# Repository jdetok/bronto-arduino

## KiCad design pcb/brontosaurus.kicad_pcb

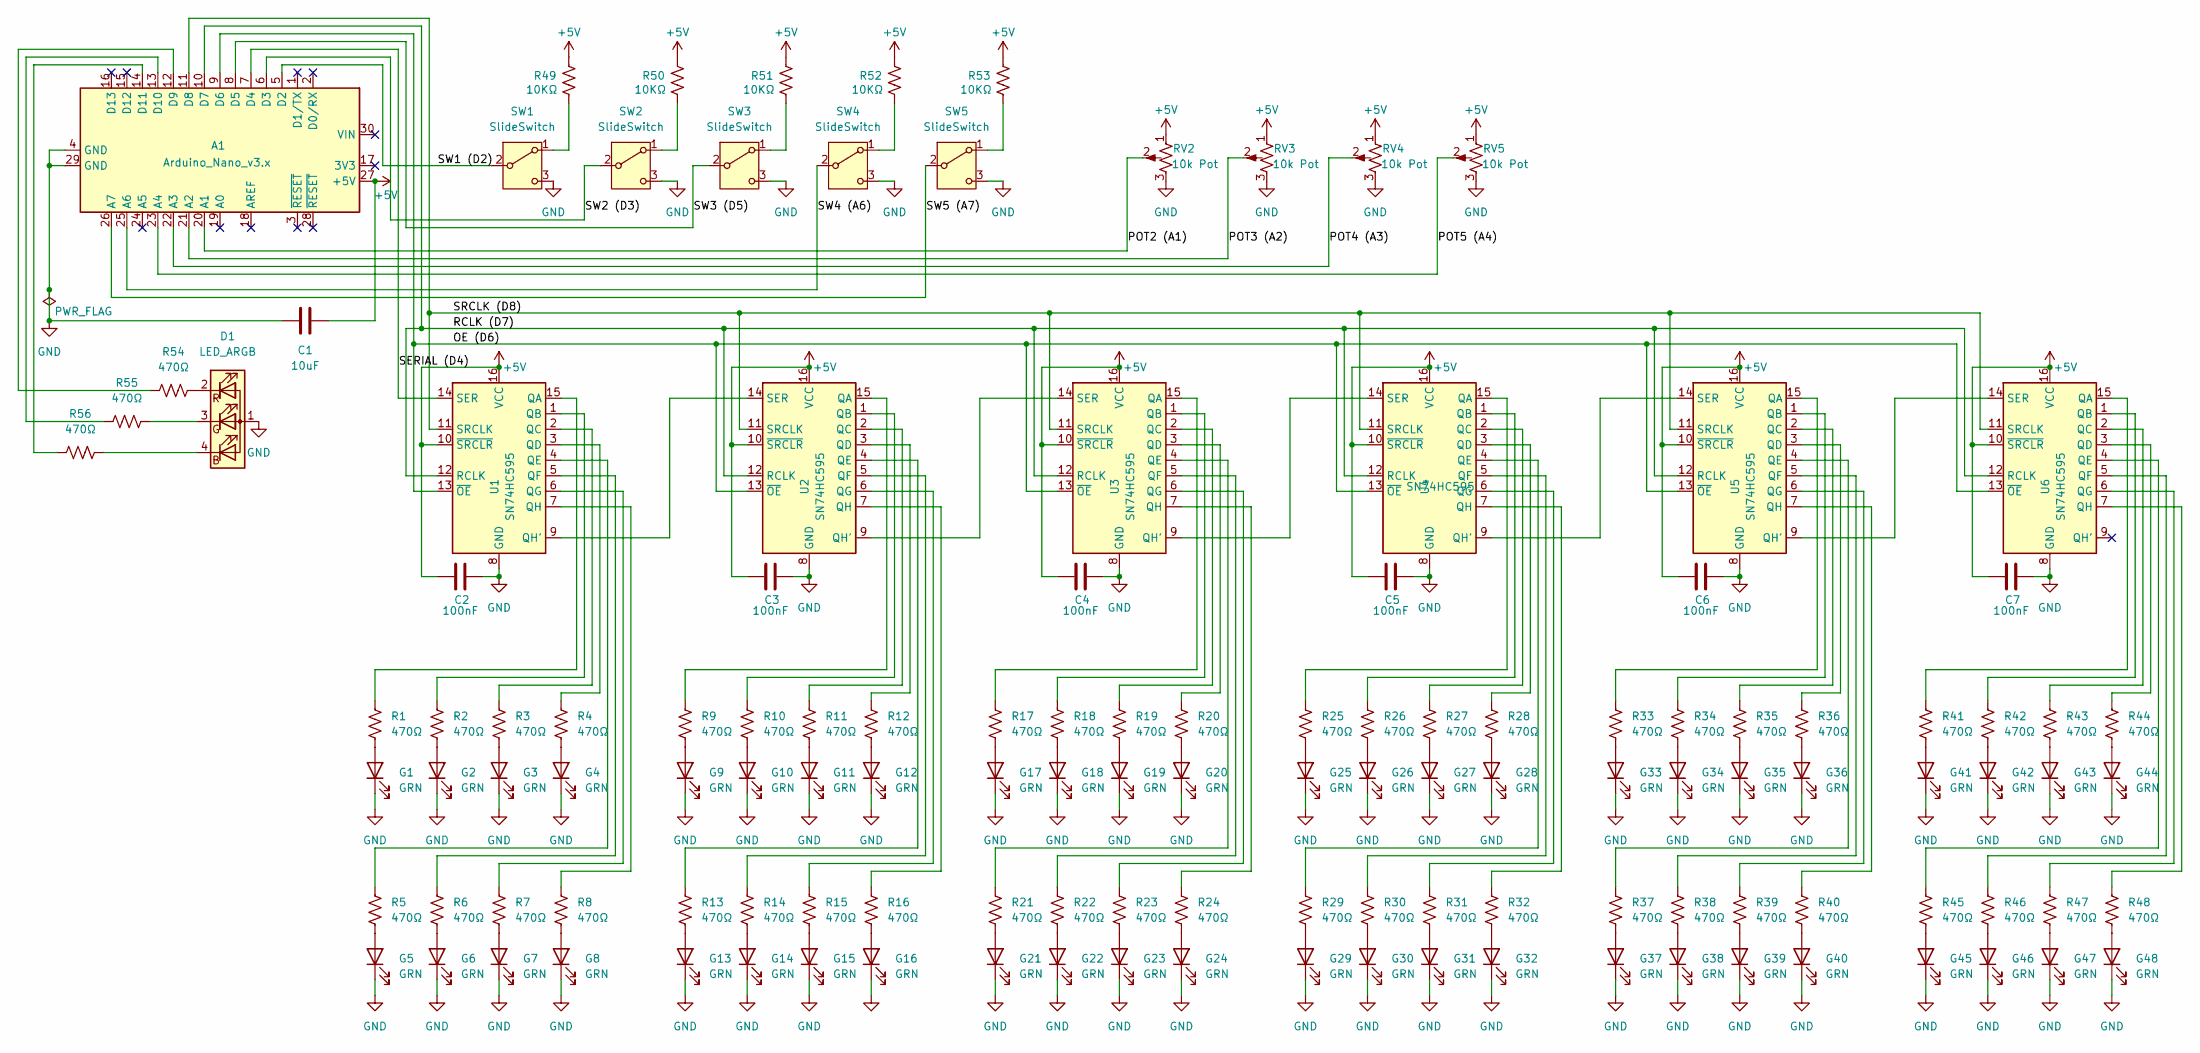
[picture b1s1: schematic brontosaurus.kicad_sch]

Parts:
A1: Arduino_Nano_v3.x; Arduino_Nano
C1: 10uF; C_Radial_D4.0mm_H5.0mm_P1.50mm
C2, C3, C4, C5, C6, C7: 100nF; C_Disc_D5.0mm_W2.5mm_P5.00mm
D1: LED_ARGB; LED_D5.0mm-4_RGB_Wide_Pins
G1, G2, G3, G4, G5, G6, G7, G8, G9, G10, G11, G12, G13, G14, G15, G16, G17, G18, G19, G20, G21, G22, G23, G24, G25, G26, G27, G28, G29, G30, G31, G32, G33, G34, G35, G36, G37, G38, G39, G40, G41, G42, G43, G44, G45, G46, G47, G48: GRN; LED_D5.0mm_Clear
R1, R2, R3, R4, R5, R6, R7, R8, R9, R10, R11, R12, R13, R14, R15, R16, R17, R18, R19, R20, R21, R22, R23, R24, R25, R26, R27, R28, R29, R30, R31, R32, R33, R34, R35, R36, R37, R38, R39, R40, R41, R42, R43, R44, R45, R46, R47, R48, R54, R55, R56: 470Ω; R_Axial_DIN0204_L3.6mm_D1.6mm_P7.62mm_Horizontal
R49, R50, R51, R52, R53: 10KΩ; R_Axial_DIN0204_L3.6mm_D1.6mm_P7.62mm_Horizontal
RV2, RV3, RV4, RV5: 10k Pot; pot_left
SW1, SW2, SW3, SW4, SW5: SlideSwitch; SlideSwitch3Pin
U1, U2, U3, U4, U5, U6: SN74HC595; 74HC595_7.62mm

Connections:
+5V: A1.27 (+5V), C1.2, C2.1, C3.1, C4.1, C5.1, C6.1, C7.1, R49.1, R50.1, R51.1, R52.1, R53.1, RV2.1, RV3.1, RV4.1, RV5.1, U1.10 (~SRCLR), U1.16 (VCC), U2.10 (~SRCLR), U2.16 (VCC), U3.10 (~SRCLR), U3.16 (VCC), U4.10 (~SRCLR), U4.16 (VCC), U5.10 (~SRCLR), U5.16 (VCC), U6.10 (~SRCLR), U6.16 (VCC)
/OE (D6): A1.9 (D6), U1.13 (~OE), U2.13 (~OE), U3.13 (~OE), U4.13 (~OE), U5.13 (~OE), U6.13 (~OE)
/POT2 (A1): A1.20 (A1), RV2.2
/POT3 (A2): A1.21 (A2), RV3.2
/POT4 (A3): A1.22 (A3), RV4.2
/POT5 (A4): A1.23 (A4), RV5.2
/RCLK (D7): A1.10 (D7), U1.12 (RCLK), U2.12 (RCLK), U3.12 (RCLK), U4.12 (RCLK), U5.12 (RCLK), U6.12 (RCLK)
/SERIAL (D4): A1.7 (D4), U1.14 (SER)
/SRCLK (D8): A1.11 (D8), U1.11 (SRCLK), U2.11 (SRCLK), U3.11 (SRCLK), U4.11 (SRCLK), U5.11 (SRCLK), U6.11 (SRCLK)
/SW1 (D2): A1.5 (D2), SW1.2 (B)
/SW2 (D3): A1.6 (D3), SW2.2 (B)
/SW3 (D5): A1.8 (D5), SW3.2 (B)
/SW4 (A6): A1.25 (A6), SW4.2 (B)
/SW5 (A7): A1.26 (A7), SW5.2 (B)
GND: A1.4 (GND), A1.29 (GND), C1.1, C2.2, C3.2, C4.2, C5.2, C6.2, C7.2, D1.1 (A), G1.1 (K), G2.1 (K), G3.1 (K), G4.1 (K), G5.1 (K), G6.1 (K), G7.1 (K), G8.1 (K), G9.1 (K), G10.1 (K), G11.1 (K), G12.1 (K), G13.1 (K), G14.1 (K), G15.1 (K), G16.1 (K), G17.1 (K), G18.1 (K), G19.1 (K), G20.1 (K), G21.1 (K), G22.1 (K), G23.1 (K), G24.1 (K), G25.1 (K), G26.1 (K), G27.1 (K), G28.1 (K), G29.1 (K), G30.1 (K), G31.1 (K), G32.1 (K), G33.1 (K), G34.1 (K), G35.1 (K), G36.1 (K), G37.1 (K), G38.1 (K), G39.1 (K), G40.1 (K), G41.1 (K), G42.1 (K), G43.1 (K), G44.1 (K), G45.1 (K), G46.1 (K), G47.1 (K), G48.1 (K), RV2.3, RV3.3, RV4.3, RV5.3, SW1.3 (C), SW2.3 (C), SW3.3 (C), SW4.3 (C), SW5.3 (C), U1.8 (GND), U2.8 (GND), U3.8 (GND), U4.8 (GND), U5.8 (GND), U6.8 (GND)
unnamed: A1.12 (D9), R54.1
unnamed: A1.13 (D10), R55.1
unnamed: A1.14 (D11), R56.1
unnamed: D1.4 (BK), R56.2
unnamed: D1.3 (GK), R55.2
unnamed: D1.2 (RK), R54.2
unnamed: G1.2 (A), R1.2
unnamed: G2.2 (A), R2.2
unnamed: G3.2 (A), R3.2
unnamed: G4.2 (A), R4.2
unnamed: G5.2 (A), R5.2
unnamed: G6.2 (A), R6.2
unnamed: G7.2 (A), R7.2
unnamed: G8.2 (A), R8.2
unnamed: G9.2 (A), R9.2
unnamed: G10.2 (A), R10.2
unnamed: G11.2 (A), R11.2
unnamed: G12.2 (A), R12.2
unnamed: G13.2 (A), R13.2
unnamed: G14.2 (A), R14.2
unnamed: G15.2 (A), R15.2
unnamed: G16.2 (A), R16.2
unnamed: G17.2 (A), R17.2
unnamed: G18.2 (A), R18.2
unnamed: G19.2 (A), R19.2
unnamed: G20.2 (A), R20.2
unnamed: G21.2 (A), R21.2
unnamed: G22.2 (A), R22.2
unnamed: G23.2 (A), R23.2
unnamed: G24.2 (A), R24.2
unnamed: G25.2 (A), R25.2
unnamed: G26.2 (A), R26.2
unnamed: G27.2 (A), R27.2
unnamed: G28.2 (A), R28.2
unnamed: G29.2 (A), R29.2
unnamed: G30.2 (A), R30.2
unnamed: G31.2 (A), R31.2
unnamed: G32.2 (A), R32.2
unnamed: G33.2 (A), R33.2
unnamed: G34.2 (A), R34.2
unnamed: G35.2 (A), R35.2
unnamed: G36.2 (A), R36.2
unnamed: G37.2 (A), R37.2
unnamed: G38.2 (A), R38.2
unnamed: G39.2 (A), R39.2
unnamed: G40.2 (A), R40.2
unnamed: G41.2 (A), R41.2
unnamed: G42.2 (A), R42.2
unnamed: G43.2 (A), R43.2
unnamed: G44.2 (A), R44.2
unnamed: G45.2 (A), R45.2
unnamed: G46.2 (A), R46.2
unnamed: G47.2 (A), R47.2
unnamed: G48.2 (A), R48.2
unnamed: R49.2, SW1.1 (A)
unnamed: R50.2, SW2.1 (A)
unnamed: R51.2, SW3.1 (A)
unnamed: R52.2, SW4.1 (A)
unnamed: R53.2, SW5.1 (A)
unnamed: R1.1, U1.15 (QA)
unnamed: R2.1, U1.1 (QB)
unnamed: R3.1, U1.2 (QC)
unnamed: R4.1, U1.3 (QD)
unnamed: R5.1, U1.4 (QE)
unnamed: R6.1, U1.5 (QF)
unnamed: R7.1, U1.6 (QG)
unnamed: U1.9 (QH'), U2.14 (SER)
unnamed: R8.1, U1.7 (QH)
unnamed: R9.1, U2.15 (QA)
unnamed: R10.1, U2.1 (QB)
unnamed: R11.1, U2.2 (QC)
unnamed: R12.1, U2.3 (QD)
unnamed: R13.1, U2.4 (QE)
unnamed: R14.1, U2.5 (QF)
unnamed: R15.1, U2.6 (QG)
unnamed: U2.9 (QH'), U3.14 (SER)
unnamed: R16.1, U2.7 (QH)
unnamed: R17.1, U3.15 (QA)
unnamed: R18.1, U3.1 (QB)
unnamed: R19.1, U3.2 (QC)
unnamed: R20.1, U3.3 (QD)
unnamed: R21.1, U3.4 (QE)
unnamed: R22.1, U3.5 (QF)
unnamed: R23.1, U3.6 (QG)
unnamed: U3.9 (QH'), U4.14 (SER)
unnamed: R24.1, U3.7 (QH)
unnamed: R25.1, U4.15 (QA)
unnamed: R26.1, U4.1 (QB)
unnamed: R27.1, U4.2 (QC)
unnamed: R28.1, U4.3 (QD)
unnamed: R29.1, U4.4 (QE)
unnamed: R30.1, U4.5 (QF)
unnamed: R31.1, U4.6 (QG)
unnamed: U4.9 (QH'), U5.14 (SER)
unnamed: R32.1, U4.7 (QH)
unnamed: R33.1, U5.15 (QA)
unnamed: R34.1, U5.1 (QB)
unnamed: R35.1, U5.2 (QC)
unnamed: R36.1, U5.3 (QD)
unnamed: R37.1, U5.4 (QE)
unnamed: R38.1, U5.5 (QF)
unnamed: R39.1, U5.6 (QG)
unnamed: U5.9 (QH'), U6.14 (SER)
unnamed: R40.1, U5.7 (QH)
unnamed: R41.1, U6.15 (QA)
unnamed: R42.1, U6.1 (QB)
unnamed: R43.1, U6.2 (QC)
unnamed: R44.1, U6.3 (QD)
unnamed: R45.1, U6.4 (QE)
unnamed: R46.1, U6.5 (QF)
unnamed: R47.1, U6.6 (QG)
unnamed: R48.1, U6.7 (QH)

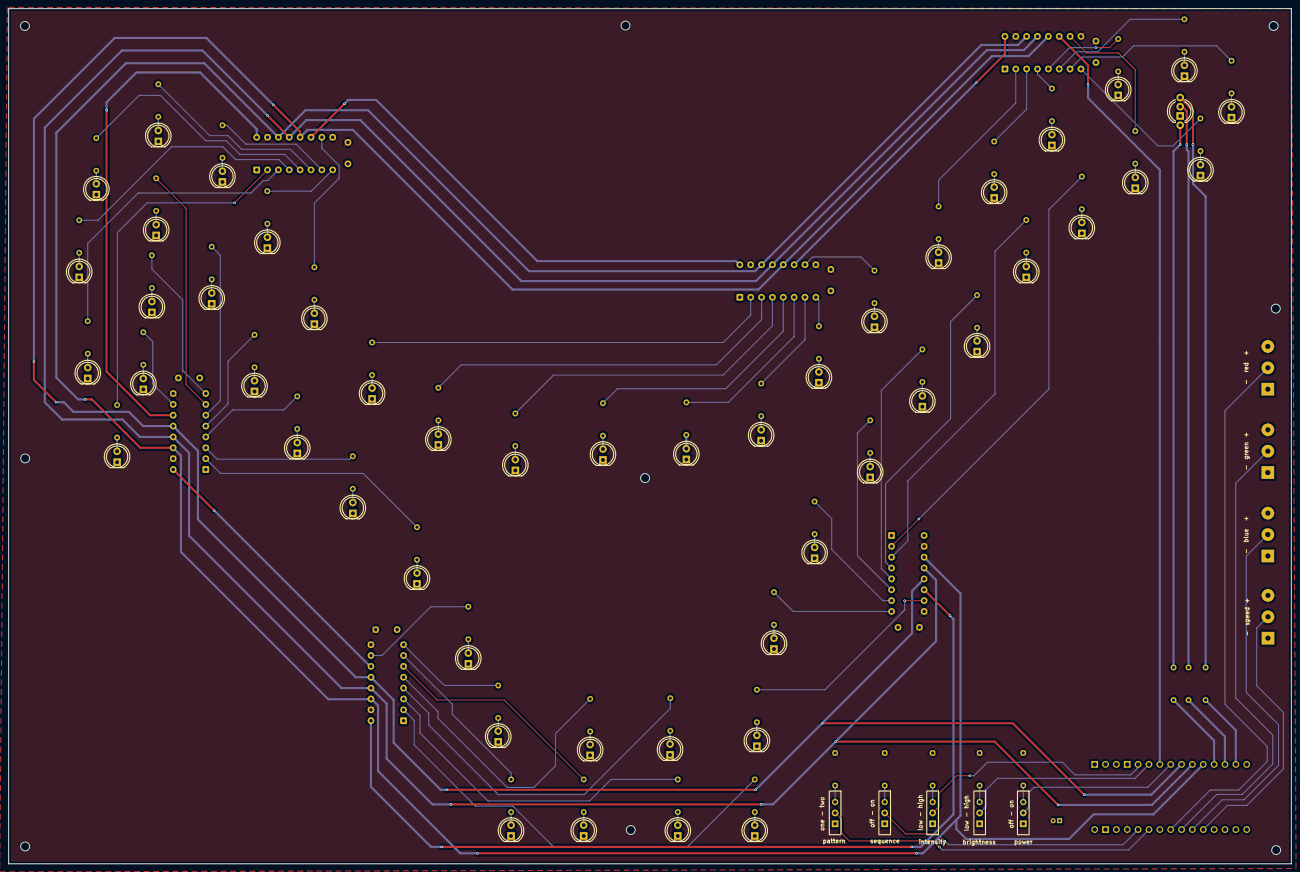
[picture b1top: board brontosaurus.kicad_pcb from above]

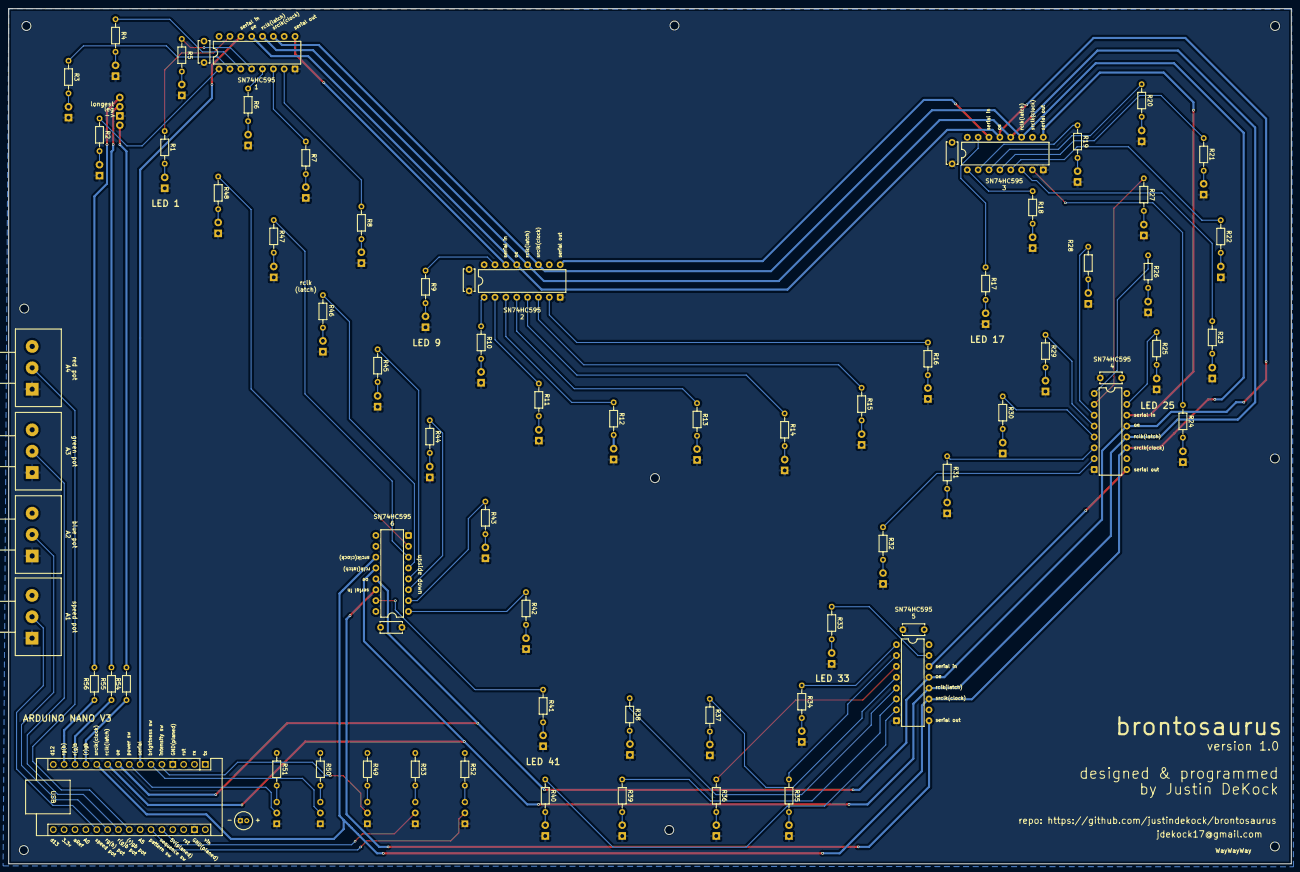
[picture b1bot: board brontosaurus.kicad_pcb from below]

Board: 2 copper layers, 300.0 x 200.0 mm, 128 parts (74 on the bottom side), 127 nets.

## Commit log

2025-04-08 created rgb class
2025-04-11 generally working, loop not working though
2025-04-14 all 48 LEDs working with preset brightness levels
2025-04-15 added rgb on off to global on off
2025-04-25 added pcb files
2025-04-28 few changes
2025-04-28 quick changes
2025-04-29 added sequence function
2025-05-01 added test cpp file to test dir with working one-at-a-time lights
2025-05-01 added led chaser function
2025-05-01 added in timing effect
2025-05-02 built PCB and started setting up code for final product
2025-05-03 improvements 5/2
2025-05-11 honestly ... pretty close to done
2025-08-09 confirmed upload works 8/8/2025
